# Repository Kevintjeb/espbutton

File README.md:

# ESPButton

This project is a clone of the AWS Dash Button. 

The idea of this project is that an ESP8266-01s sleeps until a button is pressed, when the button is pressed the ESP8266 does a certain action and goes back to sleep.

Keep in mind, this is all prototyping.

The circuit contains a Lipo battery charging circuit, as well as a NPN transistor to make sure the ESP can't be reset while it is operating.
GPIO16 is high when the ESP is in deepSleep, RESET needs to be connected to GND to wake up.

# Repo content
This repository contains the source code, written in Visual Studio Code with the Platformio extension. 

The PCB files are also included. As well as a initial 3D printed case design.

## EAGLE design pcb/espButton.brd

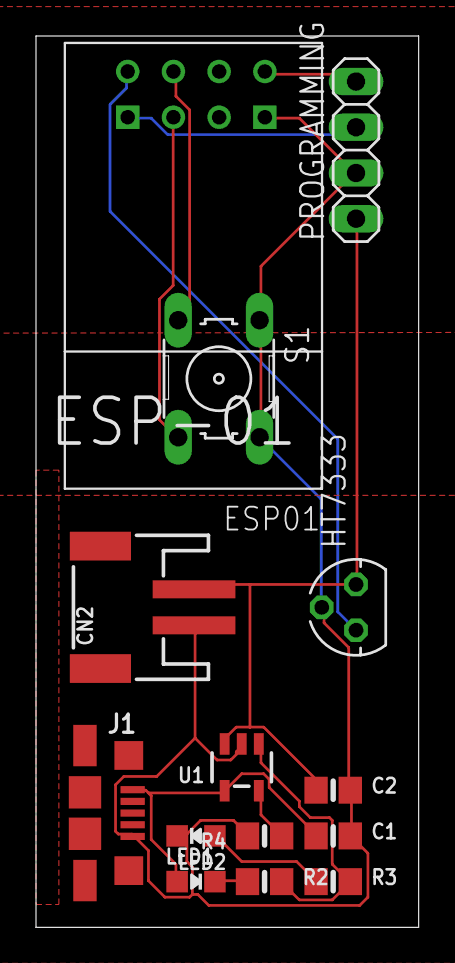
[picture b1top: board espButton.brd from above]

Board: 2 copper layers, 21.3 x 49.5 mm, 14 parts (0 on the bottom side), 12 nets.

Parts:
C1, C2: 10µF; 0805-NO
CN2: JSTPH; JSTPH2
ESP01: ESP01
HT7333: 78LXX
J1: 1981584-1
LED1: RED; CHIPLED_0805_NOOUTLINE
LED2: GREEN; CHIPLED_0805_NOOUTLINE
PROGRAMMING: 1X04
R2, R3: 470; 0805-NO
R4: 10K\; 0805-NO
S1: B3F-10XX
U1: MCP73831T-2ACI/OT; SOT23-5

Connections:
3V3: ESP01.VCC, HT7333.OUT
BAT: C2.1, CN2.2, HT7333.IN, PROGRAMMING.1, U1.3
GND: C1.2, C2.2, CN2.1, ESP01.GND, HT7333.GND, J1.5, LED2.C, PROGRAMMING.2, R4.2, S1.1, S1.2, U1.2
unnamed: C1.1, J1.1, LED1.A, U1.4
unnamed: LED1.C, R2.1
unnamed: ESP01.RST, S1.3
unnamed: R2.2, R3.2, U1.1
unnamed: R4.1, U1.5
unnamed: LED2.A, R3.1
PRGM: ESP01.GPIO0, S1.4
RX: ESP01.TX, PROGRAMMING.4
TX: ESP01.RX, PROGRAMMING.3

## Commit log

2018-02-23 Initial commit. First setup of source code and 3D design + pcb.
2018-02-23 Changed filetype of pcb images to .PNG
2018-02-23 Changed readme.md
2018-06-15 Improved pcb design

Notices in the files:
parts and their libraries:
microbuilder: This work is placed in the public domain, and may be freely used for commercial and non-commercial work with the following conditions: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
